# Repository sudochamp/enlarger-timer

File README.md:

> [!WARNING]
> This project is a work in progress. It functions, but not where I want it yet.

# Darkroom Enlarger Timer

Built to address a simple problem. I just needed a simple timer that could do stop calculations and was accurate enough to be used in a darkroom.

It will need an off-the-shelf AC/DC power supply for the 120/240VAC to 12VDC conversion.

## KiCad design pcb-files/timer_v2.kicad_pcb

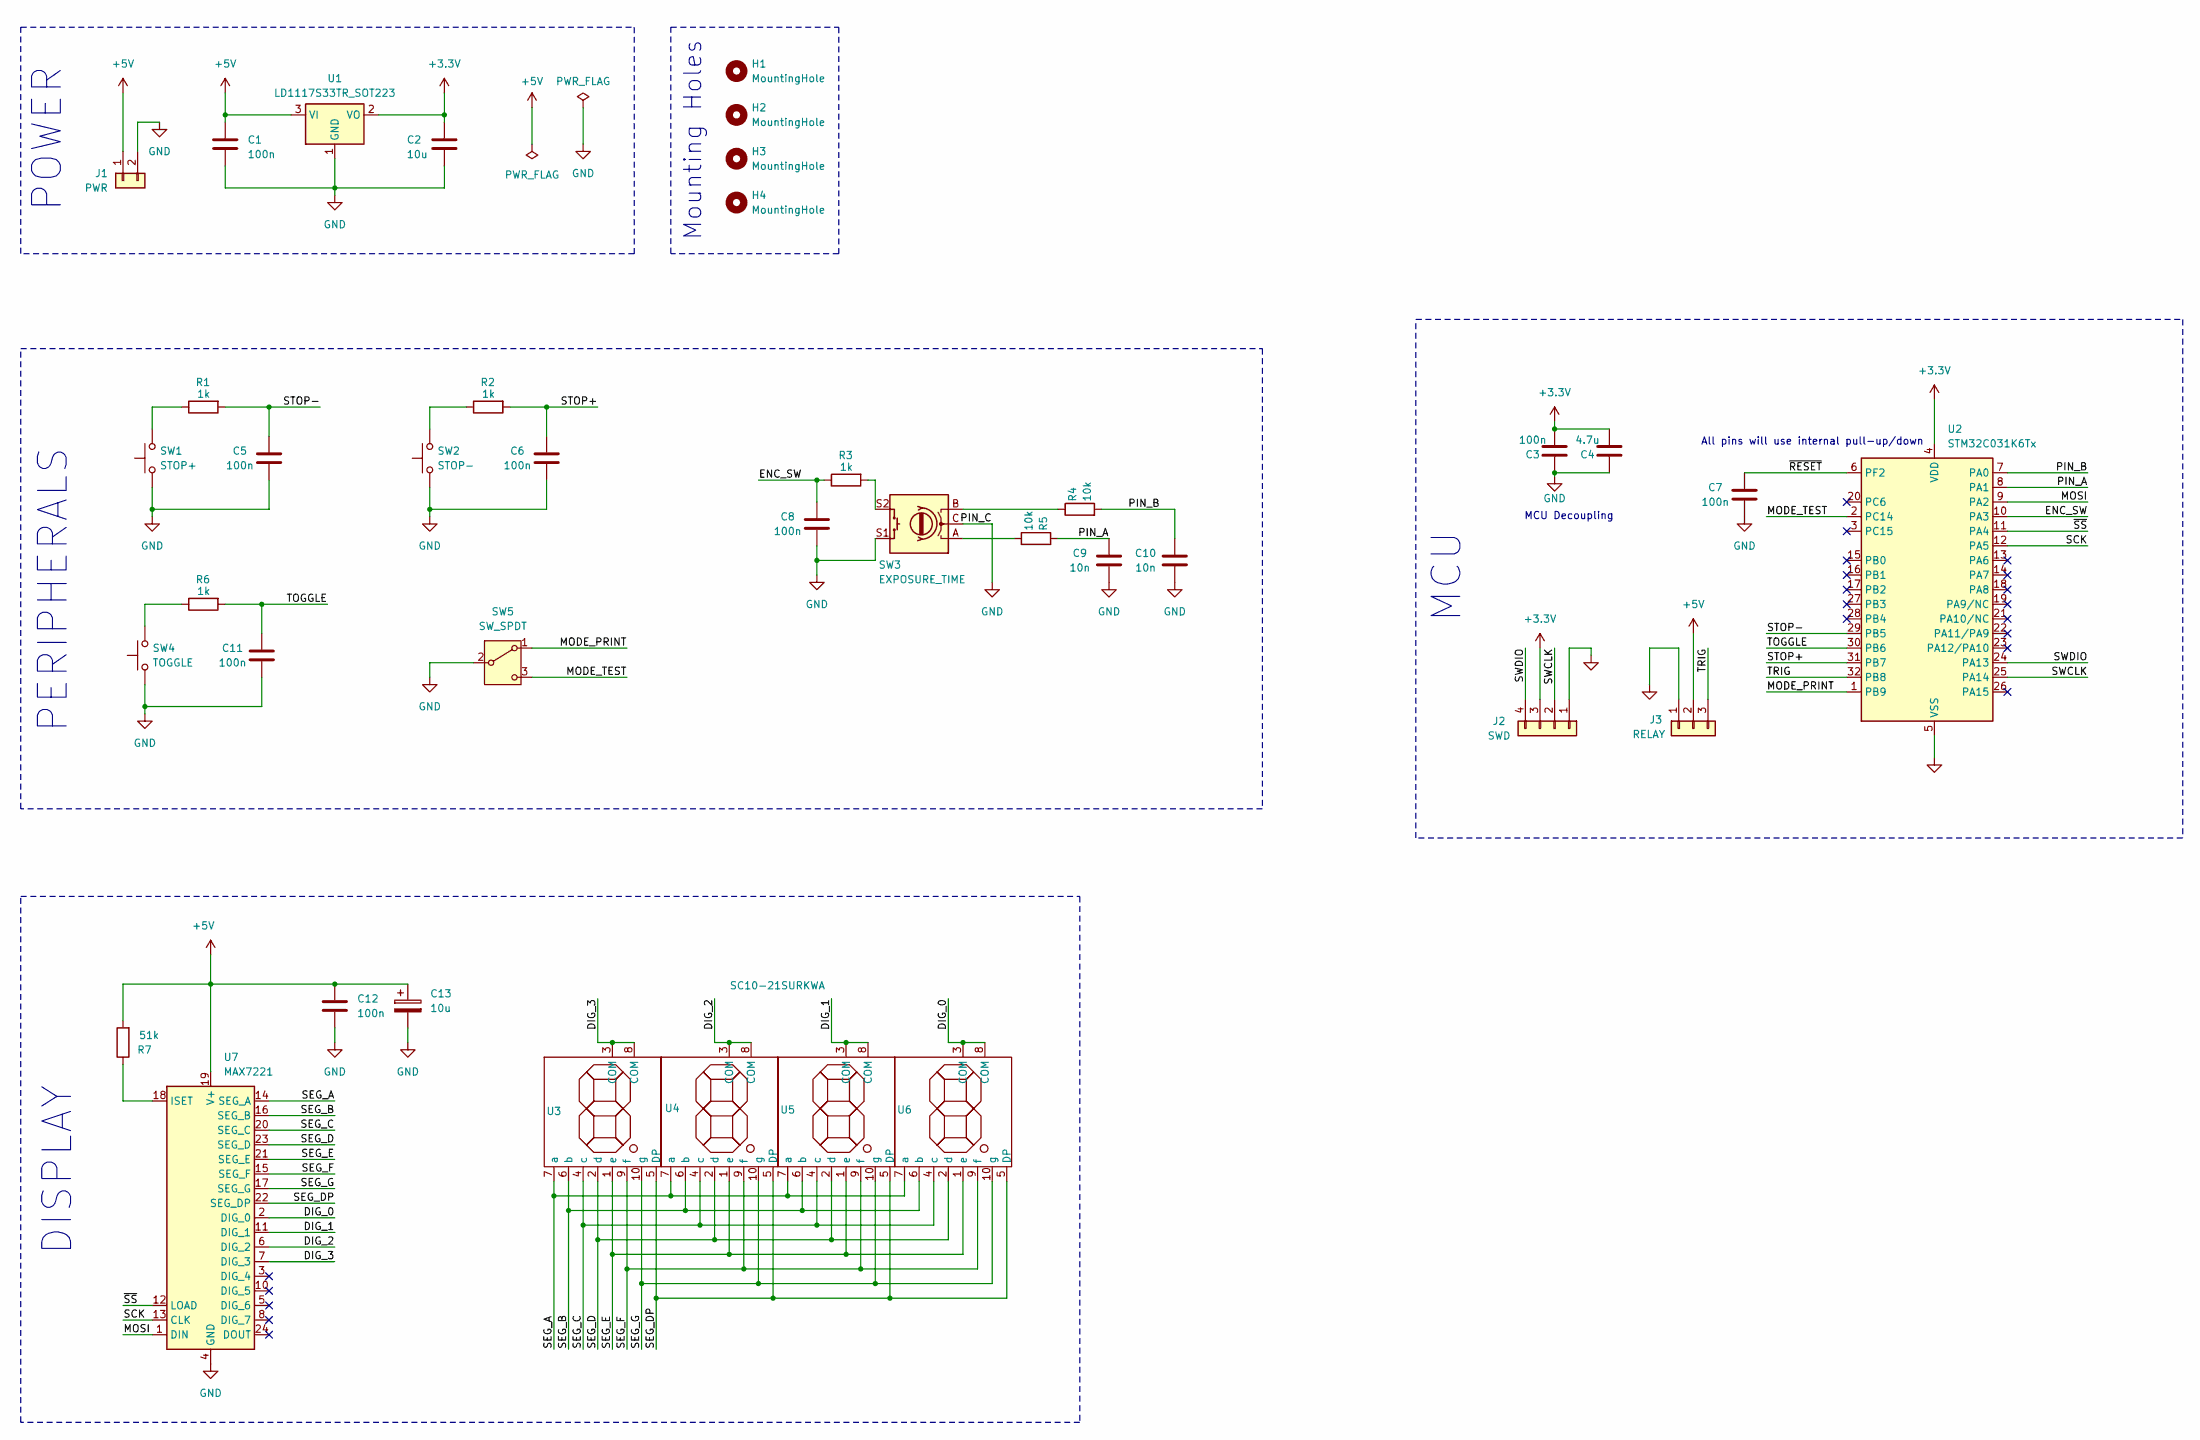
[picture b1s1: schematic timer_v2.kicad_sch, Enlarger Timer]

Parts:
C1, C8: 100n; C_0603_1608Metric; LCSC Part Number C5299898
C2: 10u; C_0603_1608Metric; LCSC Part Number C5299898
C3: 100n; C_0603_1608Metric; LCSC Part # C1525
C4: 4.7u; C_0603_1608Metric; LCSC Part # C1779
C5, C6, C7, C11, C12: 100n; C_0603_1608Metric; LCSC Part Number C2687355
C9, C10: 10n; C_0603_1608Metric; LCSC Part Number C5299898
C13: 10u; CP_Elec_4x5.4; LCSC Part Number C4747971
H1, H2, H3, H4: MountingHole; MountingHole_3.2mm_M3
J1: PWR; JST_VH_B2P-VH_1x02_P3.96mm_Vertical; LCSC Part Number C158007
J2: SWD; PinHeader_1x04_P2.54mm_Vertical
J3: RELAY; JST_XH_B3B-XH-A_1x03_P2.50mm_Vertical; LCSC Part Number C158007
R1, R2, R3, R6: 1k; R_0603_1608Metric; LCSC Part Number C5123581
R4, R5: 10k; R_0603_1608Metric; LCSC Part Number C5123581
R7: 51k; R_0603_1608Metric; LCSC Part Number C5355236
SW1: STOP+; SW_Kailh_Choc_V2_THT_nSilk; JLCPCB_Footprint SW_Kailh_Choc_V1V2_1.00u
SW2: STOP-; SW_Kailh_Choc_V2_THT_nSilk; JLCPCB_Footprint SW_Kailh_Choc_V1V2_1.00u
SW3: EXPOSURE_TIME; RotaryEncoder_Alps_EC11E-Switch_Vertical_H20mm; JLCPCB_Footprint RotaryEncoder_Alps_EC11E-Switch_Vertica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
SW4: TOGGLE; SW_Kailh_Choc_V2_THT_nSilk; JLCPCB_Footprint SW_Kailh_Choc_V1V2_1.00u
SW5: SW_SPDT; Switch_Toggle_SPDT_SubMini; JLCPCB_Footprint Switch_Toggle_SPDT_Mini_SolderLug
U1: LD1117S33TR_SOT223; SOT-223-3_TabPin2; JLCPCB_Footprint SOT-223-3_TabPin2
U2: STM32C031K6Tx; LQFP-32_7x7mm_P0.8mm; JLCPCB_Footprint LQFP-32_7x7mm_P0.8mm
U3, U4, U5, U6: SC10-21SURKWA
U7: MAX7221; SOIC-24W_7.5x15.4mm_P1.27mm; LCSC Part Number C6705351

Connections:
+3.3V: C2.1, C3.2, C4.2, J2.3, U1.2 (VO), U2.4 (VDD)
+5V: C1.1, C12.1, C13.1, J1.1, J3.2, R7.2, U1.3 (VI), U7.19 (V+)
/DIG_0: U6.3 (COM), U6.8 (COM), U7.2 (DIG_0)
/DIG_1: U5.3 (COM), U5.8 (COM), U7.11 (DIG_1)
/DIG_2: U4.3 (COM), U4.8 (COM), U7.6 (DIG_2)
/DIG_3: U3.3 (COM), U3.8 (COM), U7.7 (DIG_3)
/ENC_SW: C8.2, R3.1, U2.10 (PA3)
/MODE_PRINT: SW5.1 (A), U2.1 (PB9)
/MODE_TEST: SW5.3 (C), U2.2 (PC14)
/MOSI: U2.9 (PA2), U7.1 (DIN)
/PIN_A: C9.2, R5.1, U2.8 (PA1)
/PIN_B: C10.2, R4.2, U2.7 (PA0)
/SCK: U2.12 (PA5), U7.13 (CLK)
/SEG_A: U3.7 (a), U4.7 (a), U5.7 (a), U6.7 (a), U7.14 (SEG_A)
/SEG_B: U3.6 (b), U4.6 (b), U5.6 (b), U6.6 (b), U7.16 (SEG_B)
/SEG_C: U3.4 (c), U4.4 (c), U5.4 (c), U6.4 (c), U7.20 (SEG_C)
/SEG_D: U3.2 (d), U4.2 (d), U5.2 (d), U6.2 (d), U7.23 (SEG_D)
/SEG_DP: U3.5 (DP), U4.5 (DP), U5.5 (DP), U6.5 (DP), U7.22 (SEG_DP)
/SEG_E: U3.1 (e), U4.1 (e), U5.1 (e), U6.1 (e), U7.21 (SEG_E)
/SEG_F: U3.9 (f), U4.9 (f), U5.9 (f), U6.9 (f), U7.15 (SEG_F)
/SEG_G: U3.10 (g), U4.10 (g), U5.10 (g), U6.10 (g), U7.17 (SEG_G)
/STOP+: C6.2, R2.2, U2.31 (PB7)
/STOP-: C5.2, R1.2, U2.29 (PB5)
/SWCLK: J2.2, U2.25 (PA14)
/SWDIO: J2.4, U2.24 (PA13)
/TOGGLE: C11.2, R6.2, U2.30 (PB6)
/TRIG: J3.3, U2.32 (PB8)
/~RESET: C7.2, U2.6 (PF2)
/~SS: U2.11 (PA4), U7.12 (LOAD)
GND: C1.2, C2.2, C3.1, C4.1, C5.1, C6.1, C7.1, C8.1, C9.1, C10.1, C11.1, C12.2, C13.2, J1.2, J2.1, J3.1, SW1.1, SW2.1, SW3.C, SW3.S1, SW4.1, SW5.2 (B), U1.1 (GND), U2.5 (VSS), U7.4 (GND), U7.9 (GND)
unnamed: R1.1, SW1.2
unnamed: R2.1, SW2.2
unnamed: R3.2, SW3.S2
unnamed: R4.1, SW3.B
unnamed: R5.2, SW3.A
unnamed: R6.1, SW4.2
unnamed: R7.1, U7.18 (ISET)

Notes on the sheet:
MCU
MCU Decoupling
Mounting Holes
POWER
All pins will use internal pull-up/down
DISPLAY
PERIPHERALS

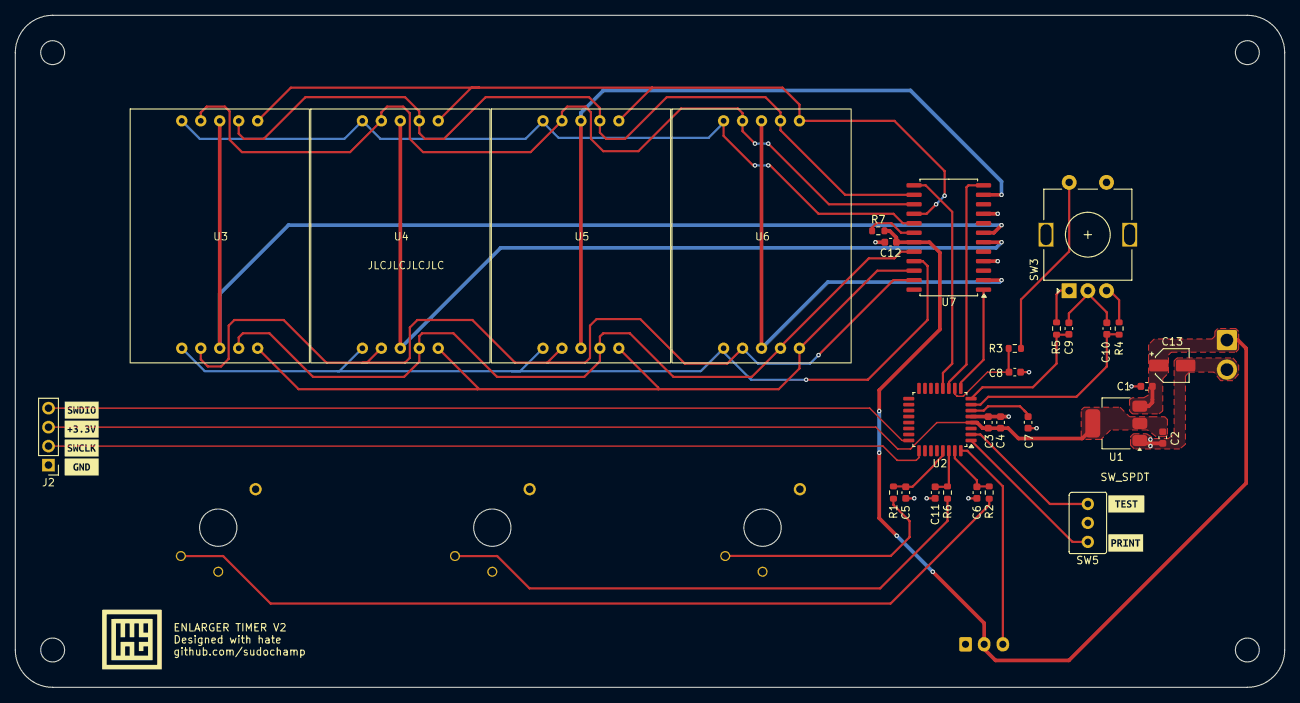
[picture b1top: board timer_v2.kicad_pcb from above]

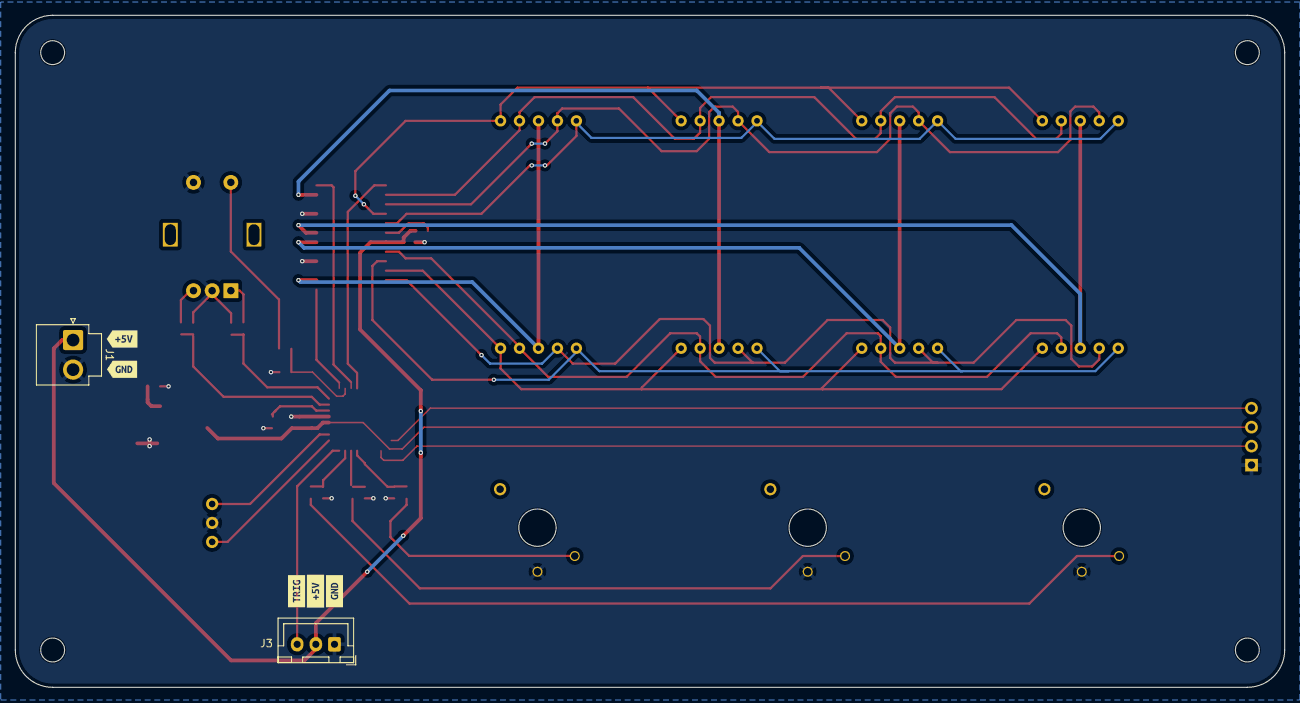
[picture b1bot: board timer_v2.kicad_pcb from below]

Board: 2 copper layers, 170.0 x 90.0 mm, 50 parts (7 on the bottom side), 37 nets.

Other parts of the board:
kibuzzard-66150B8E: G***; kibuzzard-66150B8E
kibuzzard-66150B83: G***; kibuzzard-66150B83
kibuzzard-66150B89: G***; kibuzzard-66150B89
kibuzzard-66150BA4: G***; kibuzzard-66150BA4
kibuzzard-66150BD0: G***; kibuzzard-66150BD0
kibuzzard-66150C4D: G***; kibuzzard-66150C4D
kibuzzard-66150C9A: G***; kibuzzard-66150C9A
kibuzzard-66150C19: G***; kibuzzard-66150C19
kibuzzard-66150C52: G***; kibuzzard-66150C52
kibuzzard-66150CEE: G***; kibuzzard-66150CEE
kibuzzard-66150D04: G***; kibuzzard-66150D04

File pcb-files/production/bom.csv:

Designator,Footprint,Quantity,Value,LCSC Part #
"C1, C11, C12, C5, C6, C7, C8",0603,7,100n,
"C10, C9",0603,2,10n,
C13,CP_Elec_4x5.4,1,10u,
C2,0603,1,10u,
C3,0603,1,100n,C1525
C4,0603,1,4.7u,C1779
"H1, H2, H3, H4",MountingHole_3.2mm_M3,4,MountingHole,
J1,JST_VH_B2P-VH_1x02_P3.96mm_Vertical,1,PWR,
J2,PinHeader_1x04_P2.54mm_Vertical,1,SWD,
J3,JST_XH_B3B-XH-A_1x03_P2.50mm_Vertical,1,RELAY,
"R1, R2, R3, R6",0603,4,1k,
"R4, R5",0603,2,10k,
R7,0603,1,51k,
SW1,SW_Kailh_Choc_V2_THT_nSilk,1,STOP+,
SW2,SW_Kailh_Choc_V2_THT_nSilk,1,STOP-,
SW3,RotaryEncoder_Alps_EC11E-Switch_Vertical_H20mm,1,EXPOSURE_TIME,
SW4,SW_Kailh_Choc_V2_THT_nSilk,1,TOGGLE,
SW5,Switch_Toggle_SPDT_SubMini,1,SW_SPDT,
U1,SOT-223-3_TabPin2,1,LD1117S33TR_SOT223,
U2,LQFP-32_7x7mm_P0.8mm,1,STM32C031K6Tx,
"U3, U4, U5, U6",SC10-21SURKWA,4,SC10-21SURKWA,
U7,SOIC-24W_7.5x15.4mm_P1.27mm,1,MAX7221,

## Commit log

2025-10-17 add files
2025-10-17 clean file structure
    - remove prl
    - include C code for the STM32
    - updated README
2025-10-17 add callout for progress
2025-10-17 update readme... again.
